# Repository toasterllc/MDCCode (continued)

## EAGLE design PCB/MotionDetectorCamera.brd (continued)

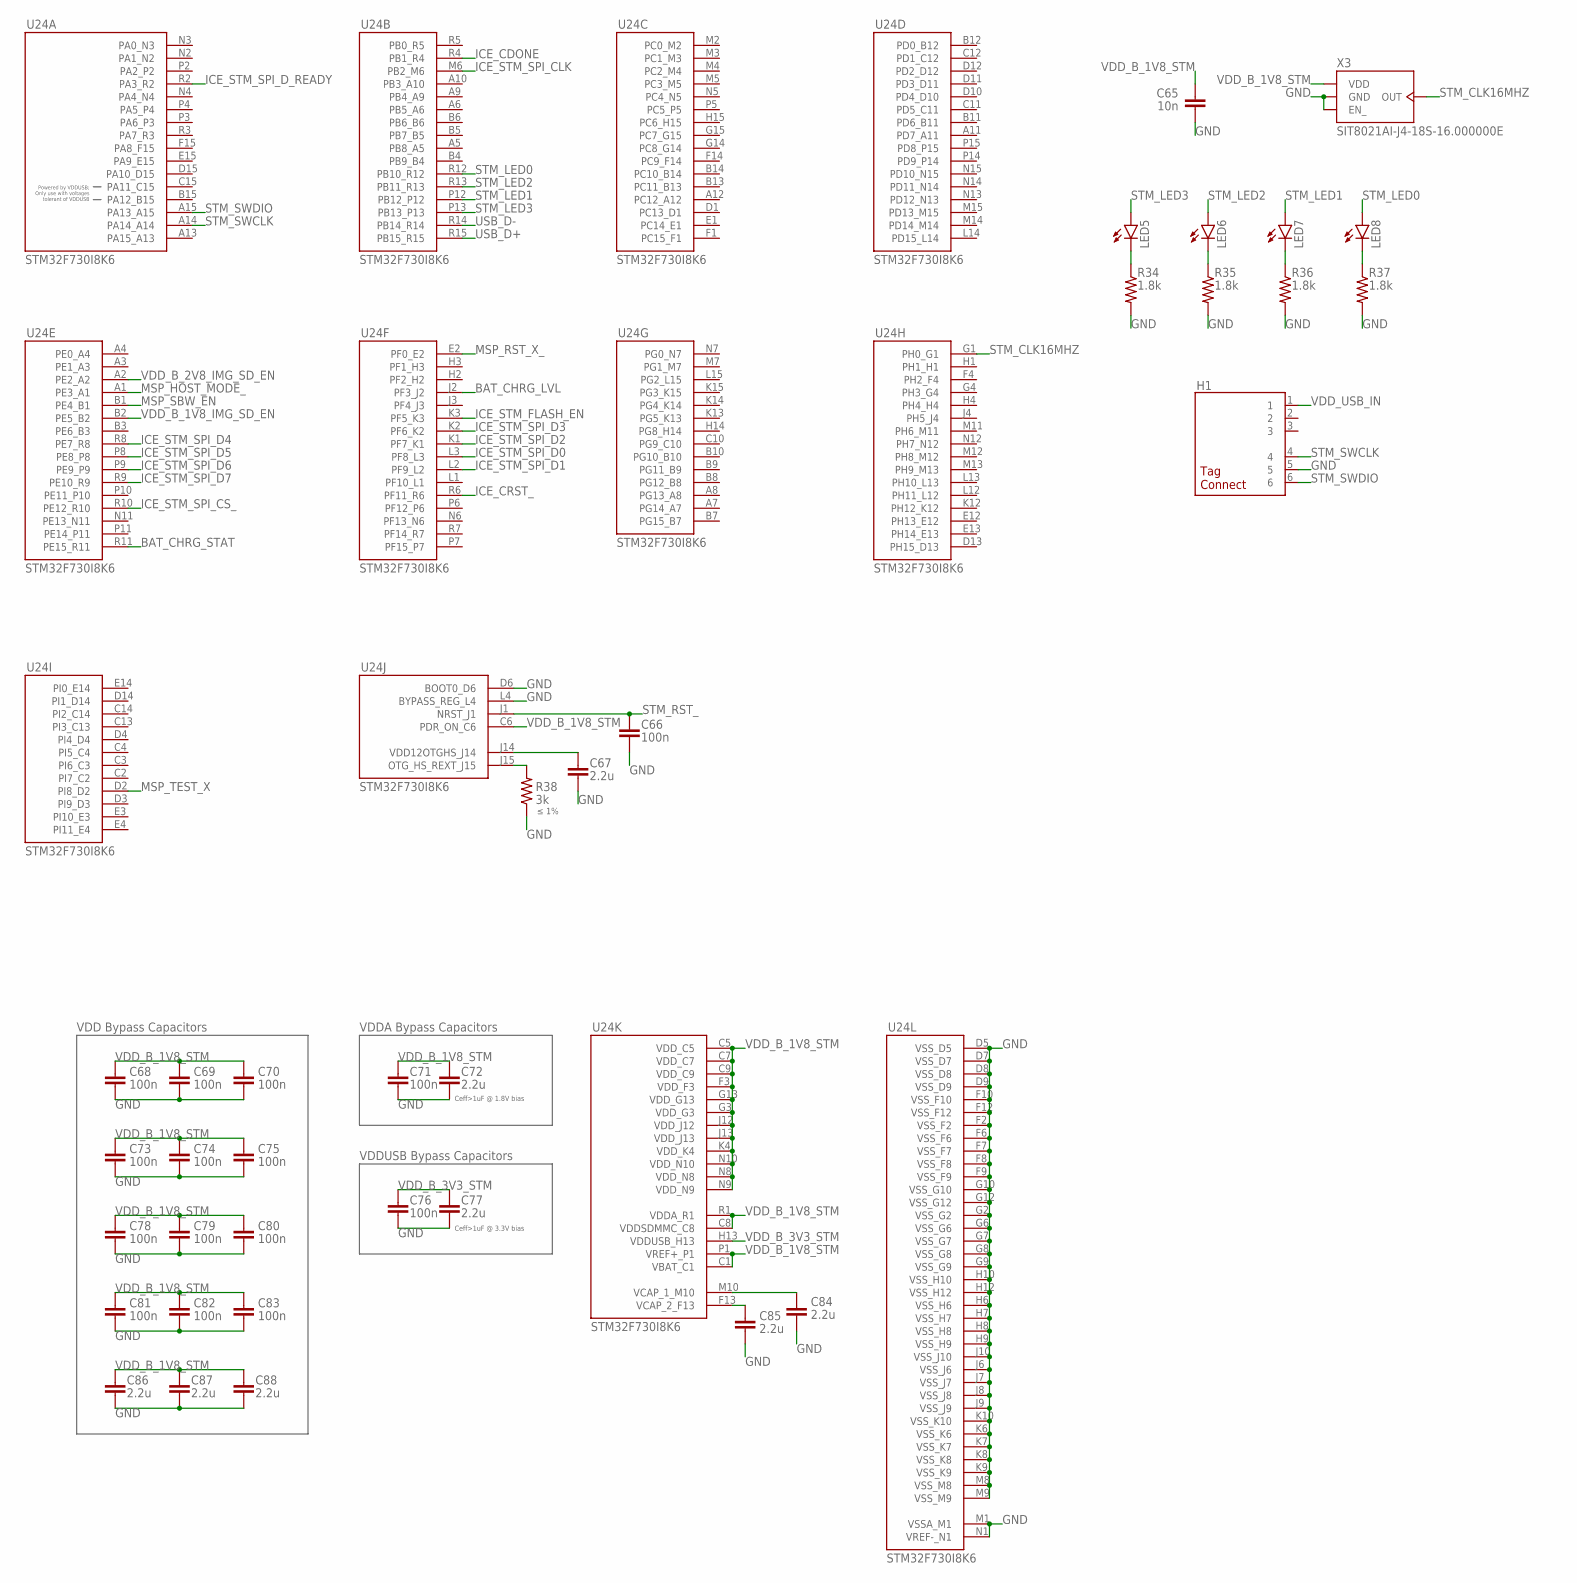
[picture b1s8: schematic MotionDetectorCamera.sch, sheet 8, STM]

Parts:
C65: 10n; 0402
C66, C68, C69, C70, C71, C73, C74, C75, C76, C78, C79, C80, C81, C82, C83: 100n; 0402
C67, C72, C77, C84, C85, C86, C87, C88: 2.2u; 0402
H1: TAGCONNECT-TC2030-NLEDGE; TAGCONNECT-TC2030-NL-EDGE
LED5, LED6, LED7, LED8: LED; LED-0603
R34, R35, R36, R37: 1.8k; 0402
R38: 3k; 0402
U24: STM-STM32F730; STM-STM32F730I8
X3: SITIME-SIT8021

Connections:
BAT_CHRG_LVL: U24.J2 (PF3_J2); also elsewhere on the board
BAT_CHRG_STAT: U24.R11 (PE15_R11); also elsewhere on the board
GND: C65.2, C66.2, C67.2, C68.2, C69.2, C70.2, C71.2, C72.2, C73.2, C74.2, C75.2, C76.2, C77.2, C78.2, C79.2, C80.2, C81.2, C82.2, C83.2, C84.2, C85.2, C86.2, C87.2, C88.2, H1.5, R34.2, R35.2, R36.2, R37.2, R38.1, U24.D5 (VSS_D5), U24.D6 (BOOT0_D6), U24.D7 (VSS_D7), U24.D8 (VSS_D8), U24.D9 (VSS_D9), U24.F2 (VSS_F2), U24.F6 (VSS_F6), U24.F7 (VSS_F7), U24.F8 (VSS_F8), U24.F9 (VSS_F9), U24.F10 (VSS_F10), U24.F12 (VSS_F12), U24.G2 (VSS_G2), U24.G6 (VSS_G6), U24.G7 (VSS_G7), U24.G8 (VSS_G8), U24.G9 (VSS_G9), U24.G10 (VSS_G10), U24.G12 (VSS_G12), U24.H6 (VSS_H6), U24.H7 (VSS_H7), U24.H8 (VSS_H8), U24.H9 (VSS_H9), U24.H10 (VSS_H10), U24.H12 (VSS_H12), U24.J6 (VSS_J6), U24.J7 (VSS_J7), U24.J8 (VSS_J8), U24.J9 (VSS_J9), U24.J10 (VSS_J10), U24.K6 (VSS_K6), U24.K7 (VSS_K7), U24.K8 (VSS_K8), U24.K9 (VSS_K9), U24.K10 (VSS_K10), U24.L4 (BYPASS_REG_L4), U24.M1 (VSSA_M1), U24.M8 (VSS_M8), U24.M9 (VSS_M9), U24.N1 (VREF-_N1), X3.1 (EN_), X3.4 (GND); also elsewhere on the board
ICE_CDONE: U24.R4 (PB1_R4); also elsewhere on the board
ICE_CRST_: U24.R6 (PF11_R6); also elsewhere on the board
ICE_STM_FLASH_EN: U24.K3 (PF5_K3); also elsewhere on the board
ICE_STM_SPI_CLK: U24.M6 (PB2_M6); also elsewhere on the board
ICE_STM_SPI_CS_: U24.R10 (PE12_R10); also elsewhere on the board
ICE_STM_SPI_D0: U24.L3 (PF8_L3); also elsewhere on the board
ICE_STM_SPI_D1: U24.L2 (PF9_L2); also elsewhere on the board
ICE_STM_SPI_D2: U24.K1 (PF7_K1); also elsewhere on the board
ICE_STM_SPI_D3: U24.K2 (PF6_K2); also elsewhere on the board
ICE_STM_SPI_D4: U24.R8 (PE7_R8); also elsewhere on the board
ICE_STM_SPI_D5: U24.P8 (PE8_P8); also elsewhere on the board
ICE_STM_SPI_D6: U24.P9 (PE9_P9); also elsewhere on the board
ICE_STM_SPI_D7: U24.R9 (PE10_R9); also elsewhere on the board
ICE_STM_SPI_D_READY: U24.R2 (PA3_R2); also elsewhere on the board
MSP_HOST_MODE_: U24.A1 (PE3_A1); also elsewhere on the board
MSP_RST_X_: U24.E2 (PF0_E2); also elsewhere on the board
MSP_SBW_EN: U24.B1 (PE4_B1); also elsewhere on the board
MSP_TEST_X: U24.D2 (PI8_D2); also elsewhere on the board
unnamed: C84.1, U24.M10 (VCAP_1_M10)
unnamed: C85.1, U24.F13 (VCAP_2_F13)
unnamed: R38.2, U24.J15 (OTG_HS_REXT_J15)
unnamed: C67.1, U24.J14 (VDD12OTGHS_J14)
unnamed: LED8.C, R37.1
unnamed: LED7.C, R36.1
unnamed: LED6.C, R35.1
unnamed: LED5.C, R34.1
STM_CLK16MHZ: U24.G1 (PH0_G1), X3.2 (OUT)
STM_LED0: LED8.A, U24.R12 (PB10_R12)
STM_LED1: LED7.A, U24.P12 (PB12_P12)
STM_LED2: LED6.A, U24.R13 (PB11_R13)
STM_LED3: LED5.A, U24.P13 (PB13_P13)
STM_RST_: C66.1, U24.J1 (NRST_J1)
STM_SWCLK: H1.4, U24.A14 (PA14_A14)
STM_SWDIO: H1.6, U24.A15 (PA13_A15)
USB_D+: U24.R15 (PB15_R15); also elsewhere on the board
USB_D-: U24.R14 (PB14_R14); also elsewhere on the board
VDD_B_1V8_IMG_SD_EN: U24.B2 (PE5_B2); also elsewhere on the board
VDD_B_1V8_STM: C65.1, C68.1, C69.1, C70.1, C71.1, C72.1, C73.1, C74.1, C75.1, C78.1, C79.1, C80.1, C81.1, C82.1, C83.1, C86.1, C87.1, C88.1, U24.C1 (VBAT_C1), U24.C5 (VDD_C5), U24.C6 (PDR_ON_C6), U24.C7 (VDD_C7), U24.C8 (VDDSDMMC_C8), U24.C9 (VDD_C9), U24.F3 (VDD_F3), U24.G3 (VDD_G3), U24.G13 (VDD_G13), U24.J12 (VDD_J12), U24.J13 (VDD_J13), U24.K4 (VDD_K4), U24.N8 (VDD_N8), U24.N9 (VDD_N9), U24.N10 (VDD_N10), U24.P1 (VREF+_P1), U24.R1 (VDDA_R1), X3.3 (VDD); also elsewhere on the board
VDD_B_2V8_IMG_SD_EN: U24.A2 (PE2_A2); also elsewhere on the board
VDD_B_3V3_STM: C76.1, C77.1, U24.H13 (VDDUSB_H13); also elsewhere on the board
VDD_USB_IN: H1.1; also elsewhere on the board

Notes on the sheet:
VDD Bypass Capacitors
VDDA Bypass Capacitors
VDDUSB Bypass Capacitors
≤ 1%
Ceff>1uF @ 3.3V bias
Ceff>1uF @ 1.8V bias

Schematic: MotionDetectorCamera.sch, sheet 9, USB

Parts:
FB1: FERRITE-BEAD0402; 0402
J11: USB-C-RECEPTACLE-KOREANHRO; KOREANHRO-TYPE-C-31-M-08A
R39, R40: 5.1k; 0402
U25: DIODESINC-DT1446-04V-7

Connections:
GND: J11.A1 (GND), J11.A12 (GND), J11.B1 (GND), J11.B12 (GND), J11.GND1 (GND), J11.GND2 (GND), J11.GND3 (GND), J11.GND4 (GND), J11.GND5 (GND), J11.GND6 (GND), J11.GND7 (GND), J11.GND8 (GND), R39.2, R40.2, U25.2 (GND); also elsewhere on the board
unnamed: J11.A5 (CC1), R39.1
unnamed: J11.B5 (CC2), R40.1
unnamed: FB1.1, J11.A4 (VBUS), J11.A9 (VBUS), J11.B4 (VBUS), J11.B9 (VBUS), U25.4 (IO3), U25.5 (VDD), U25.6 (IO4)
USB_D+: J11.A6 (D+), J11.B6 (D+), U25.3 (IO2); also elsewhere on the board
USB_D-: J11.A7 (D-), J11.B7 (D-), U25.1 (IO1); also elsewhere on the board
VDD_USB_IN: FB1.2; also elsewhere on the board

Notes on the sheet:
Low-pass filter using ferrite bead and bulk capacitance on +VDD net. Based on CurrentSensor design. Ferrite bead specs: - Rated current >> actual current (to prevent bead saturation) - Low DC resistance - Low resonant peaking
5.1k resistor requirements: - Tolerance = 10% (20% is acceptable, but 10% is required if, in the future, we want to sense the source's current capability (by reading the voltage on CC1/CC2), to potentially draw more than 500mA if the source supports it.)

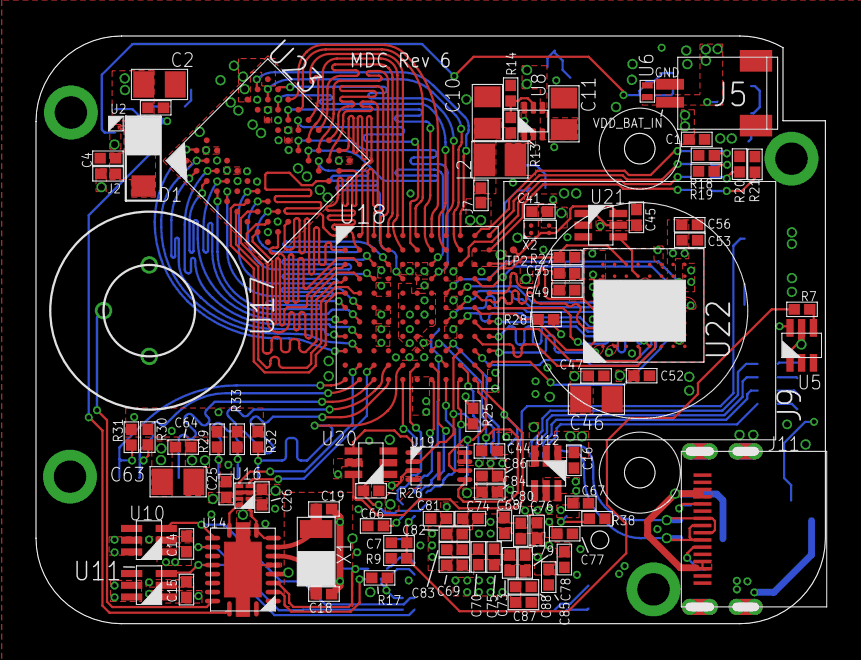
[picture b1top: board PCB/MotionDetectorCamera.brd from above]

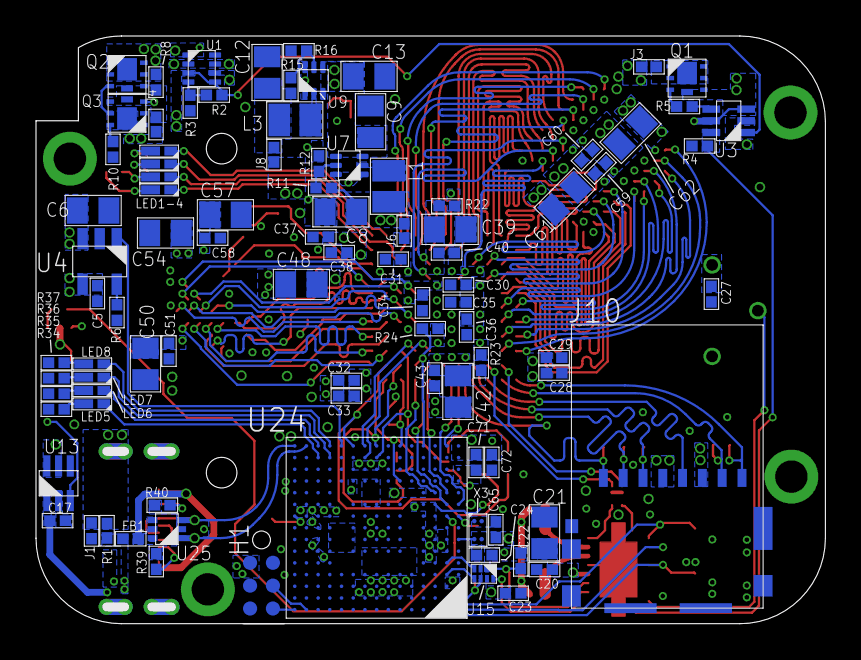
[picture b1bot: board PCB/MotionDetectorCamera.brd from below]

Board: 4 copper layers, 43.9 x 32.6 mm, 185 parts (93 on the bottom side), 163 nets.

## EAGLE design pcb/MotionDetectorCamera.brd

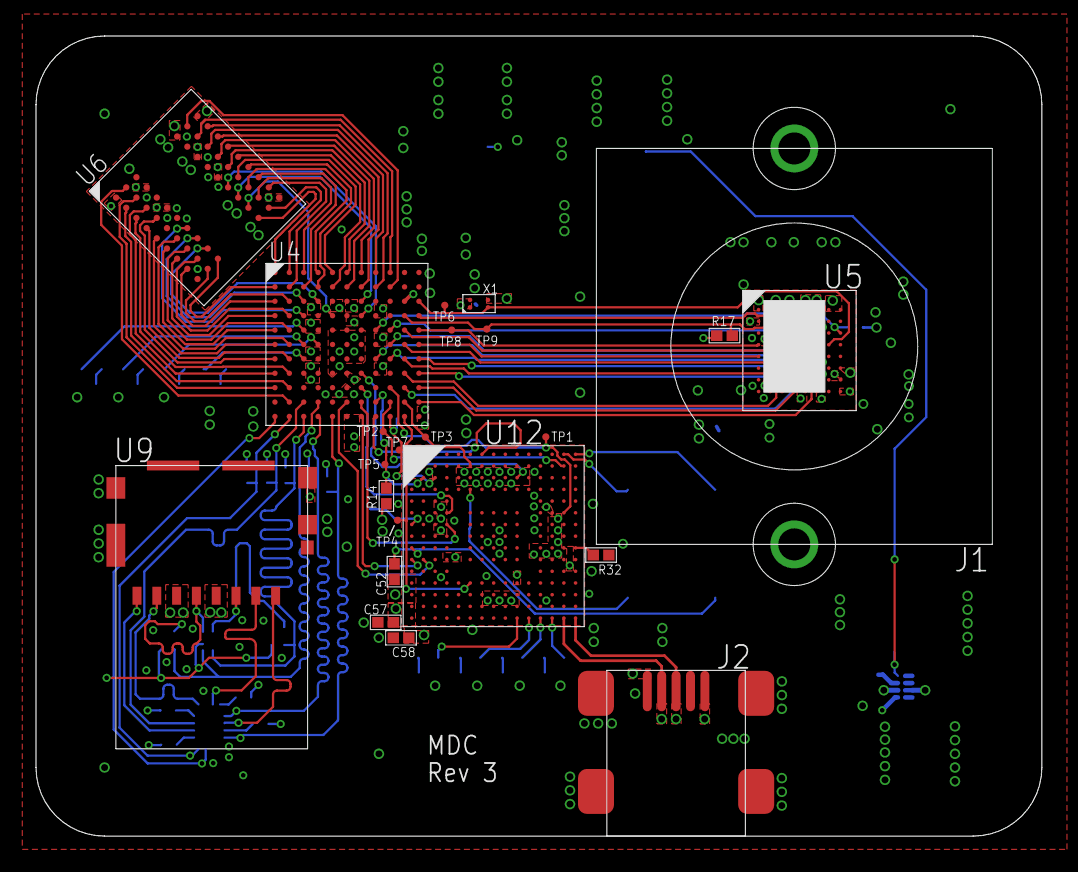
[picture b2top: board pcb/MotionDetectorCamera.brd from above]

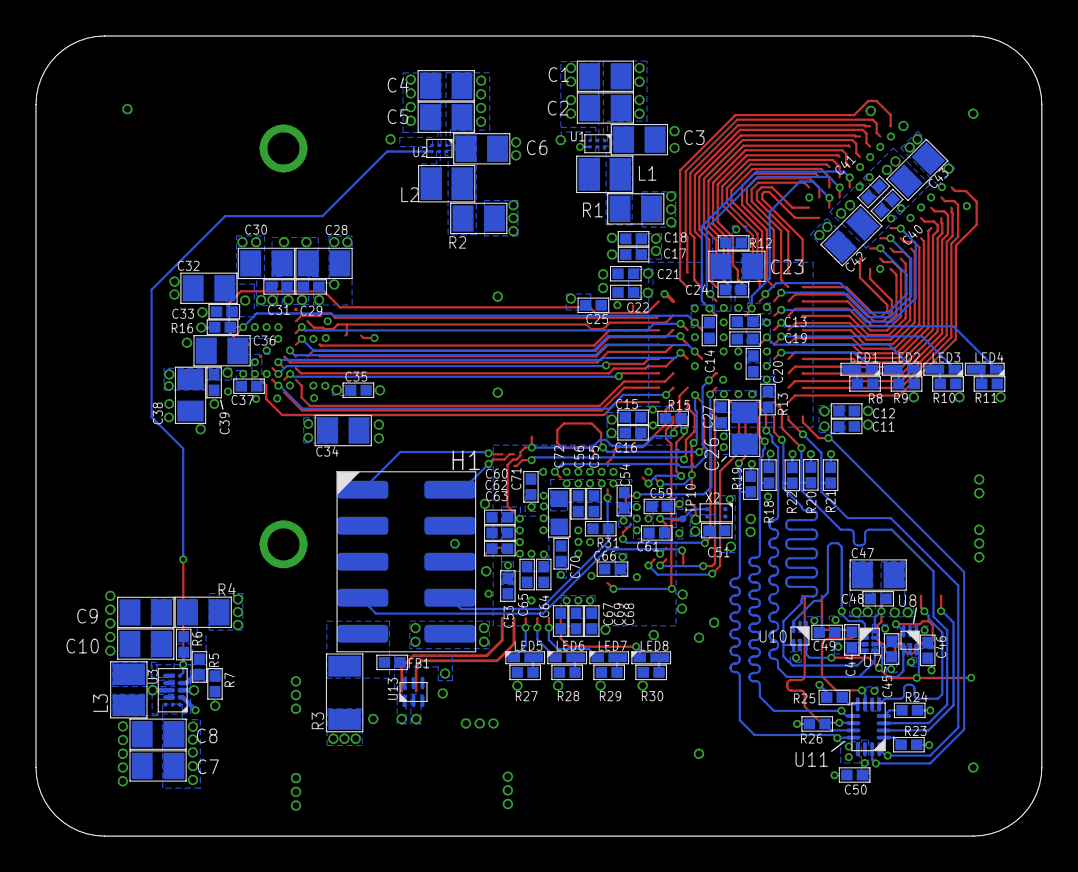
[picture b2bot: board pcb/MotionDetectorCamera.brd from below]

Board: 4 copper layers, 55.9 x 44.5 mm, 144 parts (121 on the bottom side), 134 nets.

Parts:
C1, C2, C3, C4, C5, C6, C7, C8, C9, C10, C23, C26, C28, C30, C32, C34, C36, C38, C42, C43, C47: 10u; 0805
C11, C13, C15, C17, C19, C21, C24, C27, C29, C31, C33, C35, C37, C39, C40, C41, C44, C45, C46, C48, C49, C50, C52, C54, C55, C56, C57, C59, C60, C61, C62, C64, C65, C66, C67, C68, C69: 100n; 0402
C12, C14, C16, C18, C20, C22, C25, C51: 10n; 0402
C53, C70, C71: 2.2u; 0402
C58, C63: 1u; 0402
C72: 4.7u; 0603
FB1: FERRITE-BEAD0402; 0402
H1: HEADER-2X5; TEC-1-2314844-0
J1: S-MOUNT-LENS-HOLDER
J2: MINI-USB-JACK; AMPHENOLFCI-10033526-N3222MLF
L1, L2, L3: 470n; 0806
LED1, LED2, LED3, LED4, LED5, LED6, LED7, LED8: LED; LED-0603
R1, R2, R4: 0; 0805
R3: 1; 1206
R5: 422k; 0402
R6, R14, R15, R16, R31: 10k; 0402
R7: 91k; 0402
R8, R9, R10, R11, R27, R28, R29, R30: 1.8k; 0402
R12, R13: 100; 0402
R17: 4.7k; 0402
R18, R19, R20, R21, R22, R23, R24, R25, R26: 56k; 0402
R32: 3k; 0402
TP1, TP2, TP3, TP4, TP5, TP6, TP7, TP8, TP9, TP10: TEST-POINT
U1, U2: TI-TPS6280XYKAR
U3: TI-TPS63805YFFR
U4: LATTICE-ICE40HX4K-BG121
U5: ON-AR0330CS1C12SPKA0
U6: W989D6DBGX6I
U7: NXP-NTB0102; NXP-NTB0102GF
U8, U10: ON-NLAS3157; ON-NLAS3157MX3TCG
U9: MICROSD-SOCKET; MOLEX-1051620001
U11: TI-TMUX1574; TI-TMUX1574RSVR
U12: STM-STM32F730; STM-STM32F730I8
U13: TI-TPD4S012DRYR
X1, X2: SITIME-SIT8021

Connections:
1V2: C11.1, C12.1, C13.1, C14.1, R1.1, R12.2, R13.2, U4.D4, U4.D8, U4.H4, U4.H8
1V8: C15.1, C16.1, C17.1, C18.1, C19.1, C20.1, C25.1, C32.1, C33.1, C34.1, C35.1, C36.1, C37.1, C40.1, C41.1, C42.1, C43.1, C44.1, C51.1, C54.1, C55.1, C56.1, C57.1, C58.1, C59.1, C60.1, C61.1, C62.1, C63.1, C64.1, C65.1, C66.1, C67.1, C68.1, C69.1, C72.1, R2.1, R14.1, R15.1, R16.2, R17.1, R18.2, R19.2, R20.2, R21.2, R22.2, U4.D6, U4.E4, U4.F8, U4.G4, U4.H6, U4.L11, U5.A7, U5.A8, U5.B1, U5.D2, U5.D5, U5.D6, U5.E5, U5.F6, U5.G2, U5.G8, U5.H5, U6.A7, U6.A9, U6.B3, U6.C7, U6.D3, U6.E7, U6.J9, U7.3, U12.C1, U12.C5, U12.C6, U12.C7, U12.C8, U12.C9, U12.F3, U12.G3, U12.G13, U12.H13, U12.J12, U12.J13, U12.K4, U12.N8, U12.N9, U12.N10, U12.P1, U12.R1, X1.3, X2.3
2V8: C21.1, C22.1, C28.1, C29.1, C30.1, C31.1, C38.1, C39.1, C45.1, C46.1, C47.1, C48.1, C49.1, C50.1, R4.1, R23.2, R24.2, R25.2, R26.2, U4.C10, U5.A1, U5.A5, U5.A6, U5.F8, U5.H6, U5.H8, U7.7, U8.1, U9.VDD, U10.1, U11.14
2V8GOOD: R6.2, U2.C2, U3.E1
GND: C1.2, C2.2, C3.2, C4.2, C5.2, C6.2, C7.2, C8.2, C9.2, C10.2, C11.2, C12.2, C13.2, C14.2, C15.2, C16.2, C17.2, C18.2, C19.2, C20.2, C21.2, C22.2, C25.2, C28.2, C29.2, C30.2, C31.2, C32.2, C33.2, C34.2, C35.2, C36.2, C37.2, C38.2, C39.2, C40.2, C41.2, C42.2, C43.2, C44.2, C45.2, C46.2, C47.2, C48.2, C49.2, C50.2, C51.2, C52.2, C53.2, C54.2, C55.2, C56.2, C57.2, C58.2, C59.2, C60.2, C61.2, C62.2, C63.2, C64.2, C65.2, C66.2, C67.2, C68.2, C69.2, C70.2, C71.2, C72.2, H1.10, J1.1, J1.2, J2.GND, J2.GND2, J2.GND3, J2.GND4, J2.GND5, R7.1, R8.2, R9.2, R10.2, R11.2, R27.2, R28.2, R29.2, R30.2, R31.1, R32.1, U1.A1, U1.C1, U2.A1, U2.C1, U3.B1, U3.C1, U3.C2, U3.C3, U4.E5, U4.E6, U4.E7, U4.F5, U4.F6, U4.F7, U4.G5, U4.G6, U4.G7, U4.H5, U5.A3, U5.B4, U5.B5, U5.B6, U5.B7, U5.C1, U5.C4, U5.C5, U5.C6, U5.D4, U5.E6, U5.G1, U5.H2, U5.H3, U6.A1, U6.A3, U6.B7, U6.C3, U6.D7, U6.E3, U6.J1, U7.2, U8.5, U9.GND1, U9.GND2, U9.GND3, U9.GND4, U9.VSS, U10.5, U11.6, U11.13, U12.D5, U12.D7, U12.D8, U12.D9, U12.F2, U12.F6, U12.F7, U12.F8, U12.F9, U12.F10, U12.F12, U12.G2, U12.G6, U12.G7, U12.G8, U12.G9, U12.G10, U12.G12, U12.H6, U12.H7, U12.H8, U12.H9, U12.H10, U12.H12, U12.J6, U12.J7, U12.J8, U12.J9, U12.J10, U12.K6, U12.K7, U12.K8, U12.K9, U12.K10, U12.L4, U12.M1, U12.M8, U12.M9, U12.N1, U13.4, X1.1, X1.4, X2.1, X2.4
GNDPLL0: C26.2, C27.2, U4.L6
GNDPLL1: C23.2, C24.2, U4.C5
ICE_CDONE: R14.2, TP5.X, U4.K8, U12.C2
ICE_CRST_: R15.2, TP7.X, U4.L9, U12.C3
ICE_LED0: LED4.A, U4.E3
ICE_LED1: LED3.A, U4.F3
ICE_LED2: LED2.A, U4.F4
ICE_LED3: LED1.A, U4.G3
ICE_PIX_CLK24MHZ: TP6.X, U4.C11, U5.D7, X1.2
ICE_SD_CLK: U4.K4, U7.5, U8.4
ICE_SD_CMD: R22.1, U4.L3, U7.4, U10.4
ICE_SD_DAT0: R21.1, U4.L2, U11.16
ICE_SD_DAT1: R20.1, U4.K3, U11.3
ICE_SD_DAT2: R19.1, U4.L5, U11.12
ICE_SD_DAT3: R18.1, U4.L4, U11.9
ICE_SD_INIT: U4.L1, U7.6, U8.6, U10.6, U11.15
ICE_SPI_CLK: TP4.X, U4.L10, U12.M6
ICE_SPI_CS_: TP3.X, U4.K10, U12.B6
ICE_SPI_D0: TP1.X, U4.J9, U12.F14
ICE_SPI_D1: TP2.X, U4.K9, U12.B14
ICE_SPI_D2: U4.L7, U12.K1
ICE_SPI_D3: U4.K6, U12.K2
ICE_SPI_D4: U4.J7, U12.F4
ICE_SPI_D5: U4.K7, U12.G4
ICE_SPI_D6: U4.H7, U12.C10
ICE_SPI_D7: U4.L8, U12.A7
unnamed: LED5.C, R27.1
unnamed: C70.1, U12.M10
unnamed: LED6.C, R28.1
unnamed: L2.1, U2.B2
unnamed: L1.1, U1.B2
unnamed: R23.1, U11.1
unnamed: C71.1, U12.F13
unnamed: C6.1, L2.2, R2.2, U2.A2
unnamed: R32.2, U12.J15
unnamed: R5.1, R7.2, U3.D1
unnamed: L3.1, U3.B2, U3.B3
unnamed: L3.2, U3.D2, U3.D3
unnamed: R24.1, U11.4
unnamed: C3.1, L1.2, R1.2, U1.A2
unnamed: R26.1, U11.11
unnamed: C9.1, C10.1, R4.2, R5.2, R6.1, U3.E2, U3.E3
unnamed: LED7.C, R29.1
unnamed: R25.1, U11.8
unnamed: LED4.C, R11.1
unnamed: C53.1, U12.J14
unnamed: LED3.C, R10.1
unnamed: LED8.C, R30.1
unnamed: LED2.C, R9.1
unnamed: LED1.C, R8.1
unnamed: FB1.1, J2.VCC, U13.6
PIX_D0: U4.K11, U5.G6
PIX_D1: U4.J10, U5.G5
PIX_D2: U4.J11, U5.H4
PIX_D3: U4.H11, U5.G4
PIX_D4: U4.G11, U5.F5
PIX_D5: U4.H10, U5.G3
PIX_D6: U4.G9, U5.F4
PIX_D7: U4.F10, U5.E4
PIX_D8: U4.G10, U5.F3
PIX_D9: U4.G8, U5.E3
PIX_D10: U4.F9, U5.D3
PIX_D11: U4.E10, U5.E2
PIX_DCLK: U4.F11, U5.E1
PIX_FV: U4.D11, U5.B3
PIX_LV: U4.E9, U5.C3
PIX_RST_: R16.1, U4.E8, U5.C8
PIX_SCLK: TP8.X, U4.E11, U5.D1
PIX_SDATA: R17.2, TP9.X, U4.D10, U5.B2
RAM_A0: U4.D5, U6.H7
RAM_A1: U4.A3, U6.H8
RAM_A2: U4.A2, U6.J8
RAM_A3: U4.A1, U6.J7
RAM_A4: U4.B1, U6.J3
RAM_A5: U4.C2, U6.J2
RAM_A6: U4.C4, U6.H3
RAM_A7: U4.D2, U6.H2
RAM_A8: U4.C1, U6.H1
RAM_A9: U4.C3, U6.G3
RAM_A10: U4.B2, U6.H9
RAM_A11: U4.E2, U6.G2
RAM_A12: U4.D1, U6.G1
RAM_BA0: U4.C7, U6.G7
RAM_BA1: U4.A4, U6.G8
RAM_CAS_: U4.D7, U6.F7
RAM_CKE: U4.D3, U6.F3
RAM_CLK: U4.F2, U6.F2
RAM_CS_: U4.B3, U6.G9
RAM_DQ0: U4.B9, U6.A8
RAM_DQ1: U4.B8, U6.B9
RAM_DQ2: U4.A9, U6.B8
RAM_DQ3: U4.B7, U6.C9
RAM_DQ4: U4.A8, U6.C8
RAM_DQ5: U4.B6, U6.D9
RAM_DQ6: U4.A7, U6.D8
RAM_DQ7: U4.B5, U6.E9
RAM_DQ8: U4.F1, U6.E1
RAM_DQ9: U4.G1, U6.D2
RAM_DQ10: U4.G2, U6.D1
RAM_DQ11: U4.H1, U6.C2
RAM_DQ12: U4.H2, U6.C1
RAM_DQ13: U4.J1, U6.B2
RAM_DQ14: U4.J2, U6.B1
RAM_DQ15: U4.K2, U6.A2
RAM_DQM0: U4.A6, U6.E8
RAM_DQM1: U4.E1, U6.F1
RAM_RAS_: U4.A5, U6.F8
RAM_WE_: U4.B4, U6.F9
SD_CLK: U7.8, U8.3, U9.CLK
SD_CMD: U7.1, U9.CMD, U10.3
SD_DAT0: U9.DAT0, U11.5
SD_DAT1: U9.DAT1, U11.2
SD_DAT2: U9.DAT2, U11.10
SD_DAT3: U9.DAT3, U11.7
STM_BOOT: H1.8, R31.2, U12.D6
STM_CLK24MHZ: TP10.X, U12.G1, X2.2
STM_LED0: LED8.A, U12.R10
STM_LED1: LED7.A, U12.R11
STM_LED2: LED6.A, U12.R12
STM_LED3: LED5.A, U12.R13
STM_RST_: C52.1, H1.7, U12.J1
STM_SWCLK: H1.2, U12.A14
STM_SWDIO: H1.1, U12.A15
USB_D+: J2.D+, U12.R15, U13.1
USB_D-: J2.D-, U12.R14, U13.2
VCCPLL0: C26.1, C27.1, R13.1, U4.J6
VCCPLL1: C23.1, C24.1, R12.1, U4.C6
VDD: C1.1, C2.1, C4.1, C5.1, C7.1, C8.1, R3.1, U1.B1, U1.C2, U2.B1, U3.A1, U3.A2, U3.A3
VDDIN: FB1.2, H1.9, R3.2

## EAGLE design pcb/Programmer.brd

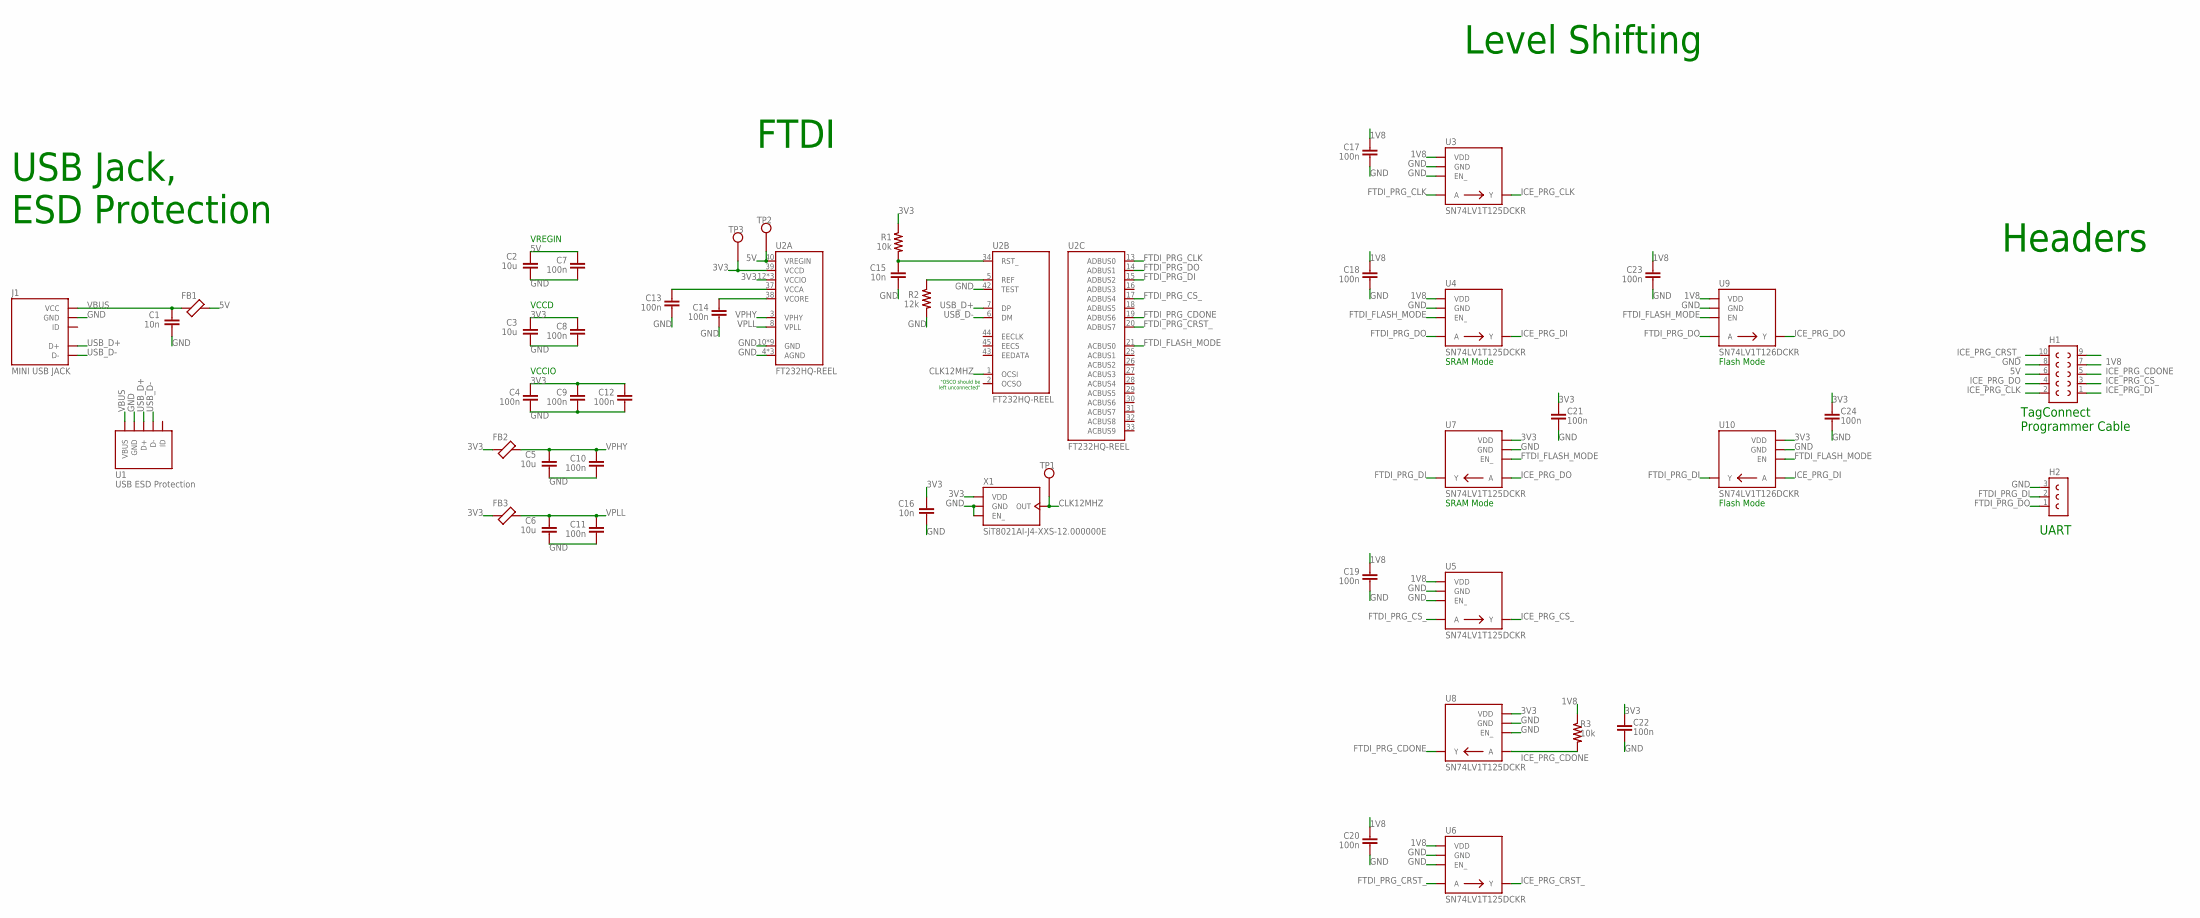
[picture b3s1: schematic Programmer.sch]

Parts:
C1, C15, C16: 10n; 0402
C2, C3, C5, C6: 10u; 1206
C4, C7, C8, C9, C10, C11, C12, C13, C14, C17, C18, C19, C20, C21, C22, C23, C24: 100n; 0402
FB1, FB2, FB3: FERRITE-BEAD1206; 1206
H1: WURTH-61201021621
H2: HEADER-1X3
J1: MINI-USB-JACK; AMPHENOLFCI-10033526-N3212MLF
R1, R3: 10k; 0402
R2: 12k; 0402
TP1, TP2, TP3: TEST-POINT
U1: TPD4S012DRYR
U2: FT232HQ
U3, U4, U5, U6, U7, U8: SN74LV1T125DCKR; SN74LV1T12XDCKR
U9, U10: SN74LV1T126DCKR; SN74LV1T12XDCKR
X1: SIT8021

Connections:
1V8: C17.1, C18.1, C19.1, C20.1, C23.1, H1.7, R3.1, U3.5 (VDD), U4.5 (VDD), U5.5 (VDD), U6.5 (VDD), U9.5 (VDD)
3V3: C3.1, C4.1, C8.1, C9.1, C12.1, C16.1, C21.1, C22.1, C24.1, FB2.1, FB3.1, R1.1, TP3.X, U2.12 (VCCIO), U2.24 (VCCIO), U2.39 (VCCD), U2.46 (VCCIO), U7.5 (VDD), U8.5 (VDD), U10.5 (VDD), X1.3 (VDD)
5V: C2.1, C7.1, FB1.2, H1.6, TP2.X, U2.40 (VREGIN)
CLK12MHZ: TP1.X, U2.1 (OCSI), X1.2 (OUT)
FTDI_FLASH_MODE: U2.21 (ACBUS0), U4.1 (EN_), U7.1 (EN_), U9.1 (EN), U10.1 (EN)
FTDI_PRG_CDONE: U2.19 (ADBUS6), U8.4 (Y)
FTDI_PRG_CLK: U2.13 (ADBUS0), U3.2 (A)
FTDI_PRG_CRST_: U2.20 (ADBUS7), U6.2 (A)
FTDI_PRG_CS_: U2.17 (ADBUS4), U5.2 (A)
FTDI_PRG_DI: H2.2, U2.15 (ADBUS2), U7.4 (Y), U10.4 (Y)
FTDI_PRG_DO: H2.1, U2.14 (ADBUS1), U4.2 (A), U9.2 (A)
GND: C1.2, C2.2, C3.2, C4.2, C5.2, C6.2, C7.2, C8.2, C9.2, C10.2, C11.2, C12.2, C13.2, C14.2, C15.2, C16.2, C17.2, C18.2, C19.2, C20.2, C21.2, C22.2, C23.2, C24.2, H1.8, H2.3, J1.GND, J1.GND2 (GND), J1.GND3 (GND), J1.GND4 (GND), J1.GND5 (GND), R2.2, U1.4 (GND), U2.4 (AGND), U2.9 (AGND), U2.10 (GND), U2.11 (GND), U2.22 (GND), U2.23 (GND), U2.35 (GND), U2.36 (GND), U2.41 (AGND), U2.42 (TEST), U2.47 (GND), U2.48 (GND), U2.49 (GND), U3.1 (EN_), U3.3 (GND), U4.3 (GND), U5.1 (EN_), U5.3 (GND), U6.1 (EN_), U6.3 (GND), U7.3 (GND), U8.1 (EN_), U8.3 (GND), U9.3 (GND), U10.3 (GND), X1.1 (EN_), X1.4 (GND)
ICE_PRG_CDONE: H1.5, R3.2, U8.2 (A)
ICE_PRG_CLK: H1.2, U3.4 (Y)
ICE_PRG_CRST_: H1.10, U6.4 (Y)
ICE_PRG_CS_: H1.3, U5.4 (Y)
ICE_PRG_DI: H1.1, U4.4 (Y), U10.2 (A)
ICE_PRG_DO: H1.4, U7.2 (A), U9.4 (Y)
unnamed: C15.1, R1.2, U2.34 (RST_)
unnamed: C13.1, U2.37 (VCCA)
unnamed: R2.1, U2.5 (REF)
unnamed: C14.1, U2.38 (VCORE)
USB_D+: J1.D+, U1.1 (D+), U2.7 (DP)
USB_D-: J1.D-, U1.2 (D-), U2.6 (DM)
VBUS: C1.1, FB1.1, J1.VCC, U1.6 (VBUS)
VPHY: C5.1, C10.1, FB2.2, U2.3 (VPHY)
VPLL: C6.1, C11.1, FB3.2, U2.8 (VPLL)

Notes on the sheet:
SRAM Mode
Flash Mode
"OSCO should be left unconnected"
VREGIN
VCCD
VCCIO
FTDI
USB Jack, ESD Protection
Level Shifting
Headers
UART
TagConnect Programmer Cable

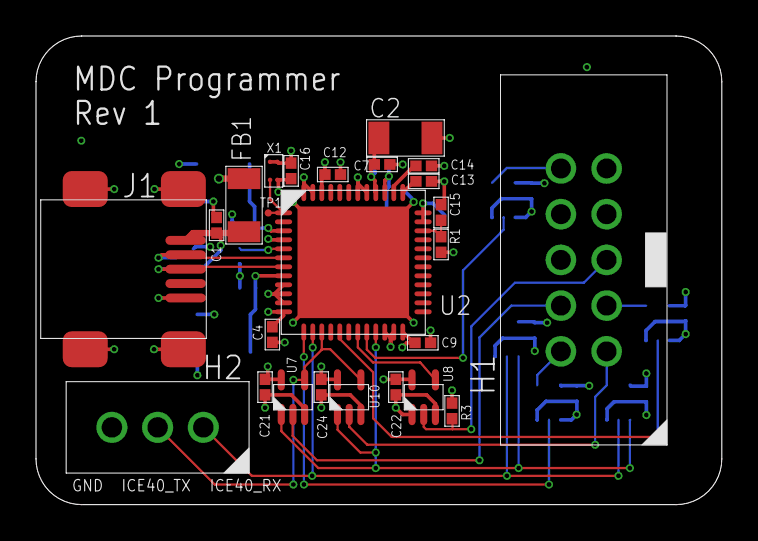
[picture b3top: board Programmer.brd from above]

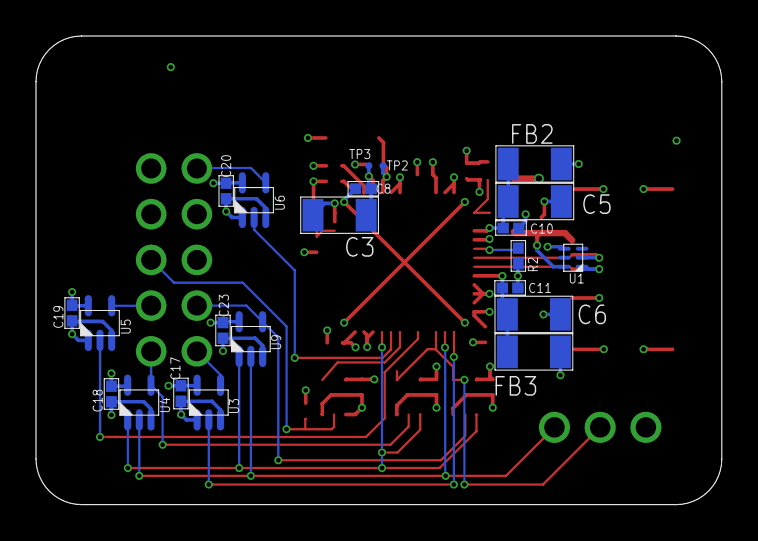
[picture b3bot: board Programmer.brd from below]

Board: 4 copper layers, 38.1 x 26.0 mm, 47 parts (22 on the bottom side), 27 nets.

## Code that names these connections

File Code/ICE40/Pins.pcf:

# Updated for board/Rev5 tag
# Sorted with `sort -V`

set_io ice_img_clk16mhz                 C11
set_io ice_led[0]                       A10
set_io ice_led[1]                       A11
set_io ice_led[2]                       C9
set_io ice_led[3]                       B11
set_io ice_msp_spi_clk                  K2
set_io ice_msp_spi_data                 K3
set_io ice_stm_spi_clk                  L10
set_io ice_stm_spi_cs_                  K10
set_io ice_stm_spi_d[0]                 L8
set_io ice_stm_spi_d[1]                 L7
set_io ice_stm_spi_d[2]                 K6
set_io ice_stm_spi_d[3]                 K7
set_io ice_stm_spi_d[4]                 J9
set_io ice_stm_spi_d[5]                 K9
set_io ice_stm_spi_d[6]                 J7
set_io ice_stm_spi_d[7]                 J8
set_io ice_stm_spi_d_ready              L5
set_io img_dclk                         F11
set_io img_d[0]                         D9
set_io img_d[1]                         D10
set_io img_d[2]                         G11
set_io img_d[3]                         G9
set_io img_d[4]                         E9
set_io img_d[5]                         K11
set_io img_d[6]                         F9
set_io img_d[7]                         G8
set_io img_d[8]                         J10
set_io img_d[9]                         J11
set_io img_d[10]                        H11
set_io img_d[11]                        H10
set_io img_fv                           E11
set_io img_lv                           E10
set_io img_rst_                         D11
set_io img_sclk                         G10
set_io img_sdata                        F10
set_io ram_a[0]                         D5
set_io ram_a[1]                         B3
set_io ram_a[2]                         B2
set_io ram_a[3]                         A1
set_io ram_a[4]                         B1
set_io ram_a[5]                         C2
set_io ram_a[6]                         C4
set_io ram_a[7]                         D2
set_io ram_a[8]                         C1
set_io ram_a[9]                         C3
set_io ram_a[10]                        A2
set_io ram_a[11]                        D1
set_io ram_ba[0]                        C7
set_io ram_ba[1]                        B4
set_io ram_cas_                         D7
set_io ram_cke                          D3
set_io ram_clk                          E1
set_io ram_cs_                          A3
set_io ram_dqm[0]                       B6
set_io ram_dqm[1]                       E2
set_io ram_dq[0]                        A9
set_io ram_dq[1]                        A8
set_io ram_dq[2]                        B9
set_io ram_dq[3]                        A7
set_io ram_dq[4]                        B8
set_io ram_dq[5]                        A6
set_io ram_dq[6]                        B7
set_io ram_dq[7]                        A5
set_io ram_dq[8]                        F2
set_io ram_dq[9]                        G2
set_io ram_dq[10]                       F1
set_io ram_dq[11]                       H2
set_io ram_dq[12]                       G1
set_io ram_dq[13]                       J2
set_io ram_dq[14]                       H1
set_io ram_dq[15]                       J1
set_io ram_ras_                         B5
set_io ram_we_                          A4
set_io sd_clk                           L3
set_io sd_cmd                           K4
set_io sd_dat[0]                        L2
set_io sd_dat[1]                        L1
set_io sd_dat[2]                        K5
set_io sd_dat[3]                        L4
set_io sd_pullup_1v8_en_                J3

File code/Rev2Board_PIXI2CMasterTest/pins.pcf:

# Rev2 board / ICE40HX4K-BG121
set_io clk12mhz         C11     -pullup no

set_io debug_clk        L10     -pullup no
set_io debug_cs         K10     -pullup no
set_io debug_di         J9      -pullup no
set_io debug_do         K9      -pullup no

set_io led[0]           G3      -pullup no
set_io led[1]           F4      -pullup no
set_io led[2]           F3      -pullup no
set_io led[3]           E3      -pullup no

set_io pix_dclk         F11     -pullup no
set_io pix_d[0]         K11     -pullup no
set_io pix_d[1]         J10     -pullup no
set_io pix_d[2]         J11     -pullup no
set_io pix_d[3]         H11     -pullup no
set_io pix_d[4]         G11     -pullup no
set_io pix_d[5]         H10     -pullup no
set_io pix_d[6]         G9      -pullup no
set_io pix_d[7]         F10     -pullup no
set_io pix_d[8]         G10     -pullup no
set_io pix_d[9]         G8      -pullup no
set_io pix_d[10]        F9      -pullup no
set_io pix_d[11]        E10     -pullup no
set_io pix_fv           D11     -pullup no
set_io pix_lv           E9      -pullup no
set_io pix_rst_         E8      -pullup no
set_io pix_sclk         E11     -pullup no
set_io pix_sdata        D10     -pullup no

set_io ram_a[0]         D5      -pullup no
set_io ram_a[1]         A3      -pullup no
set_io ram_a[2]         A2      -pullup no
set_io ram_a[3]         A1      -pullup no
set_io ram_a[4]         B1      -pullup no
set_io ram_a[5]         C2      -pullup no
set_io ram_a[6]         C4      -pullup no
set_io ram_a[7]         D2      -pullup no
set_io ram_a[8]         C1      -pullup no
set_io ram_a[9]         C3      -pullup no
set_io ram_a[10]        B2      -pullup no
set_io ram_a[11]        E2      -pullup no
set_io ram_a[12]        D1      -pullup no
set_io ram_ba[0]        C7      -pullup no
set_io ram_ba[1]        A4      -pullup no
set_io ram_cas_         D7      -pullup no
set_io ram_cke          D3      -pullup no
set_io ram_clk          F2      -pullup no
set_io ram_cs_          B3      -pullup no
set_io ram_dq[0]        B9      -pullup no
set_io ram_dq[1]        B8      -pullup no
set_io ram_dq[2]        A9      -pullup no
set_io ram_dq[3]        B7      -pullup no
set_io ram_dq[4]        A8      -pullup no
set_io ram_dq[5]        B6      -pullup no
set_io ram_dq[6]        A7      -pullup no
set_io ram_dq[7]        B5      -pullup no
set_io ram_dq[8]        F1      -pullup no
set_io ram_dq[9]        G1      -pullup no
set_io ram_dq[10]       G2      -pullup no
set_io ram_dq[11]       H1      -pullup no
set_io ram_dq[12]       H2      -pullup no
set_io ram_dq[13]       J1      -pullup no
set_io ram_dq[14]       J2      -pullup no
set_io ram_dq[15]       K2      -pullup no
set_io ram_dqm[0]       A6      -pullup no
set_io ram_dqm[1]       E1      -pullup no
set_io ram_ras_         A5      -pullup no
set_io ram_we_          B4      -pullup no

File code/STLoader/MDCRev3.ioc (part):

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Mcu.Name=STM32F730I8Kx
Mcu.Package=UFBGA176
Mcu.UserName=STM32F730I8Kx
PB10.GPIOParameters=GPIO_Label
PB10.GPIO_Label=STM_LED2
PB10.Signal=GPIO_Output
PB11.GPIOParameters=GPIO_Label
PB11.GPIO_Label=STM_LED3
PB11.Signal=GPIO_Output
PB14.Mode=Internal_Phy_Device
PB14.Signal=USB_OTG_HS_DM
PB15.Mode=Internal_Phy_Device
PB15.Signal=USB_OTG_HS_DP
PE12.GPIOParameters=GPIO_Label
PE12.GPIO_Label=STM_LED0
PE12.Signal=GPIO_Output
PE15.GPIOParameters=GPIO_Label
PE15.GPIO_Label=STM_LED1
PE15.Signal=GPIO_Output
PH0-OSC_IN.Mode=HSE-External-Clock-Source
PH0-OSC_IN.Signal=RCC_OSC_IN
PH1-OSC_OUT.Mode=HSE-External-Clock-Source
PH1-OSC_OUT.Signal=RCC_OSC_OUT
RCC.HSE_VALUE=24000000
RCC.SYSCLKFreq_VALUE=128000000
RCC.SYSCLKSource=RCC_SYSCLKSOURCE_PLLCLK
board=custom
